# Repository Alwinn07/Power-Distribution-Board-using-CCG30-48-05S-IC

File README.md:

# Power-Distribution-Board-using-CCG30-48-05S-IC
An isolated 30 W DC-DC power converter PCB based on the CCG30 module, featuring surge protection, EMI filtering, current limiting, reverse polarity protection, and robust power input circuitry. Designed in KiCad with optimized PCB layout, thermal management, and manufacturability for reliable industrial applications.

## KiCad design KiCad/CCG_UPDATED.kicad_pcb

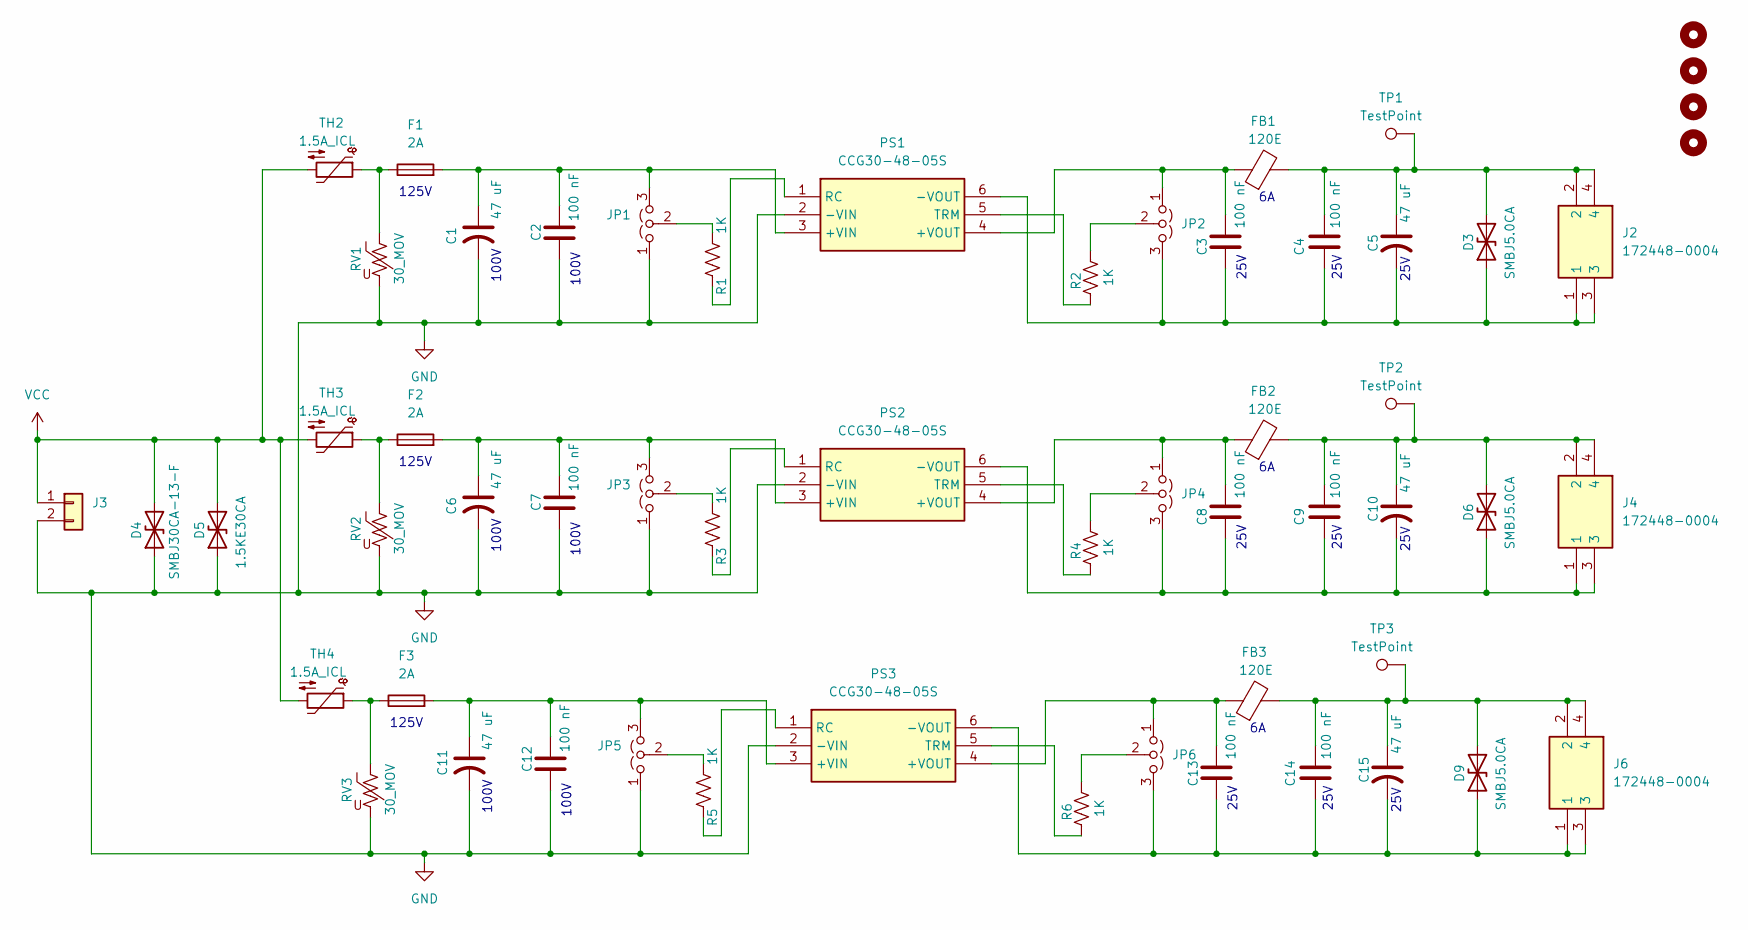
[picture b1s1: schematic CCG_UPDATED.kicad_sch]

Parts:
C1, C6, C11: 47 uF; CAPAE1300X1400N
C2, C7, C12: 100 nF; C_1206_3216Metric
C3, C4, C8, C9, C13, C14: 100 nF; C_0805_2012Metric
C5, C10, C15: 47 uF; CAPAE660X730N
D3, D6, D9: SMBJ5.0CA; D_SMB
D4: SMBJ30CA-13-F; D_SMB
D5: 1.5KE30CA; D_DO-201AD_P15.24mm_Horizontal
F1, F2, F3: 2A; FUSC10130X300N
FB1, FB2, FB3: 120E; R_1206_3216Metric
H1, H2, H3, H4: MountingHole; MountingHole_3mm_Pad
J2, J4, J6: 172448-0004; 172448-YY04; Mouser Part Number 538-172448-0004
J3: Conn_01x02; AMASS_XT60-M_1x02_P7.20mm_Vertical
JP1, JP2, JP3, JP4, JP5, JP6: Jumper_3_Open; SolderJumper-3_P1.3mm_Open_Pad1.0x1.5mm
PS1, PS2, PS3: CCG30-48-05S; CCG304815S; Mouser Part Number 967-CCG304805S
R1, R2, R3, R4, R5, R6: 1K; R_0805_2012Metric
RV1, RV2, RV3: 30_MOV; varistor.pretty
TH2, TH3, TH4: 1.5A_ICL; icl.pretty
TP1, TP2, TP3: TestPoint; TestPoint_Pad_D1.5mm

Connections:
GND: C1.2, C2.2, C6.2, C7.2, C11.2, C12.2, D4.1 (A1), D5.1 (A1), J3.2, JP1.1 (A), JP3.1 (A), JP5.1 (A), PS1.2 (-VIN), PS2.2 (-VIN), PS3.2 (-VIN), RV1.2, RV2.2, RV3.2
unnamed: C3.2, C4.2, C5.2, D3.1 (A1), J2.1, J2.3, JP2.3 (B), PS1.6 (-VOUT)
unnamed: C4.1, C5.1, D3.2 (A2), FB1.2, J2.2, J2.4, TP1.1 (1_1)
unnamed: C8.2, C9.2, C10.2, D6.1 (A1), J4.1, J4.3, JP4.3 (B), PS2.6 (-VOUT)
unnamed: C9.1, C10.1, D6.2 (A2), FB2.2, J4.2, J4.4, TP2.1 (1_1)
unnamed: C13.2, C14.2, C15.2, D9.1 (A1), J6.1, J6.3, JP6.3 (B), PS3.6 (-VOUT)
unnamed: C14.1, C15.1, D9.2 (A2), FB3.2, J6.2, J6.4, TP3.1 (1_1)
unnamed: F1.1, RV1.1, TH2.1
unnamed: F2.1, RV2.1, TH3.1
unnamed: F3.1, RV3.1, TH4.1
unnamed: C1.1, C2.1, F1.2, JP1.3 (B), PS1.3 (+VIN)
unnamed: JP1.2 (C), R1.1
unnamed: C3.1, FB1.1, JP2.1 (A), PS1.4 (+VOUT)
unnamed: JP2.2 (C), R2.1
unnamed: C6.1, C7.1, F2.2, JP3.3 (B), PS2.3 (+VIN)
unnamed: JP3.2 (C), R3.1
unnamed: C8.1, FB2.1, JP4.1 (A), PS2.4 (+VOUT)
unnamed: JP4.2 (C), R4.1
unnamed: C11.1, C12.1, F3.2, JP5.3 (B), PS3.3 (+VIN)
unnamed: JP5.2 (C), R5.1
unnamed: C13.1, FB3.1, JP6.1 (A), PS3.4 (+VOUT)
unnamed: JP6.2 (C), R6.1
unnamed: PS1.1 (RC), R1.2
unnamed: PS1.5 (TRM), R2.2
unnamed: PS2.1 (RC), R3.2
unnamed: PS2.5 (TRM), R4.2
unnamed: PS3.1 (RC), R5.2
unnamed: PS3.5 (TRM), R6.2
VCC: D4.2 (A2), D5.2 (A2), J3.1, TH2.2, TH3.2, TH4.2

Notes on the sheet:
125V
25V
100V

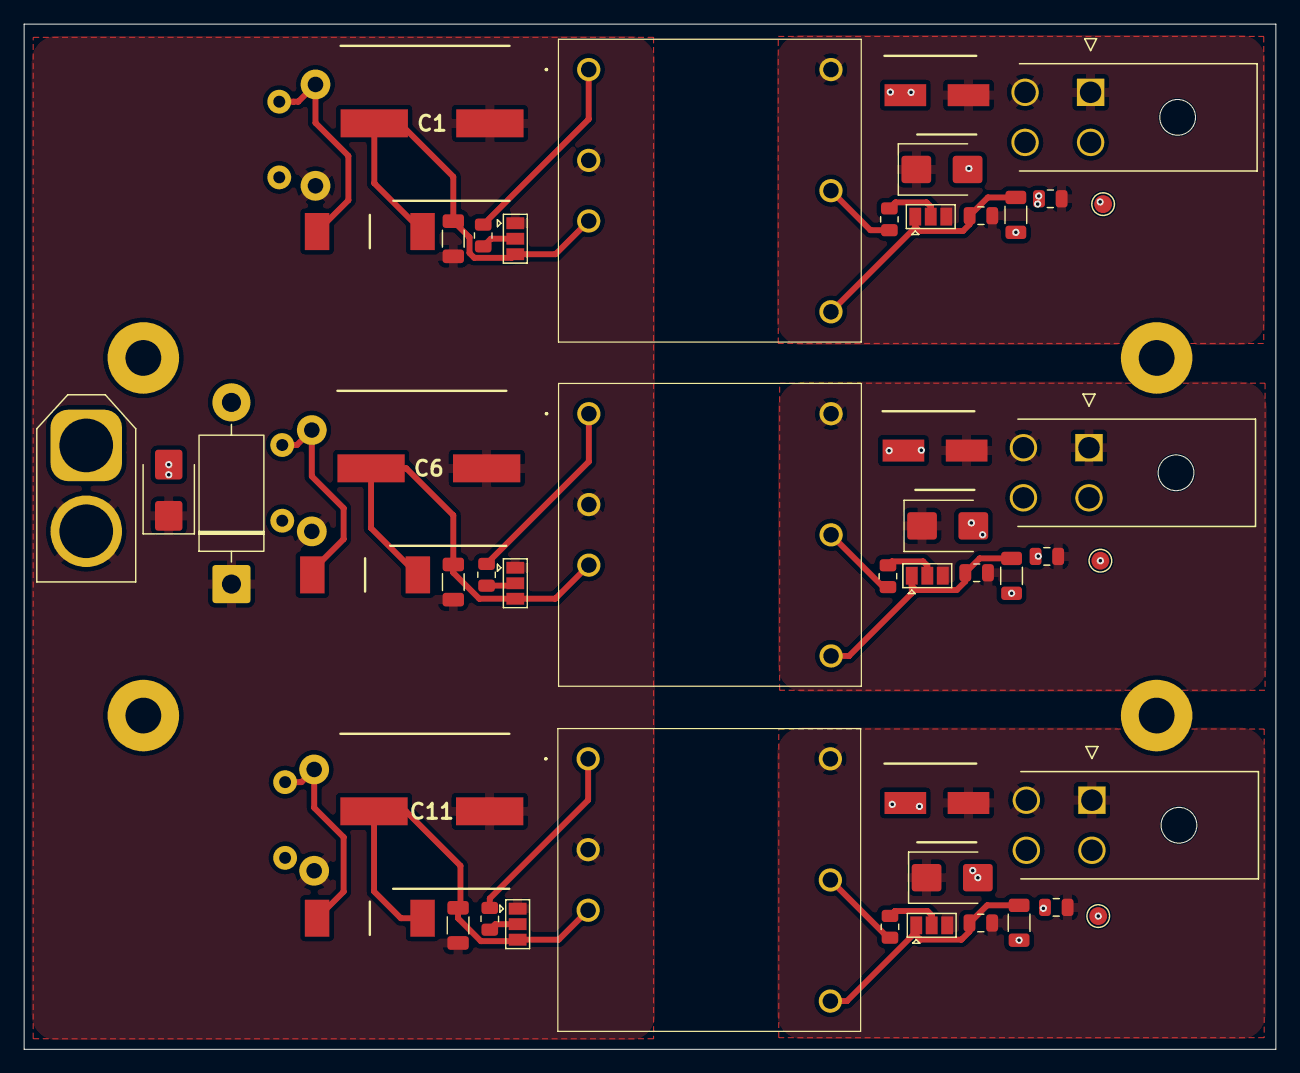
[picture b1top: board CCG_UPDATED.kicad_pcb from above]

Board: 2 copper layers, 105.0 x 86.0 mm, 58 parts (0 on the bottom side), 29 nets.
